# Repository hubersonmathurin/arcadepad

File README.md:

# Arcadepad
Arcadepad is a 6 key retro-themed macropad. It comes with a rotary encoder, an OLED display, and utilizes kmk firmware. The attached program allows switching through 3 layers, for a total of 18 commonly used 3d and 2d commands

This design was inspired by HackClub's HackPad tutorial
## Cad Model: Fusion 360

This macropad consists of 2 printed pieces, the case, which holds the PCB, and the cover. The PCB screws into 4 mounting holes, which will be filled with M3 bolts and heatset inserts, located at the bottom of the cover, not visible in picture. The case is held together with 4 more heatset inserts and M3 boots. 
## PCB: KiCad

## Bill Of Materials
- Cherry MX Switches(6)
- Blank DSA Keycaps(6)
- Seeed XIAO RP2040(1)
- EC11 Rotary Encoder(1)
- SSD1306 OLED Display(1)
- M3X13 Screws(8)
- M3x5mmx4mm Heatset Inserts(8)
- 3D Printes Case & Cover(1)

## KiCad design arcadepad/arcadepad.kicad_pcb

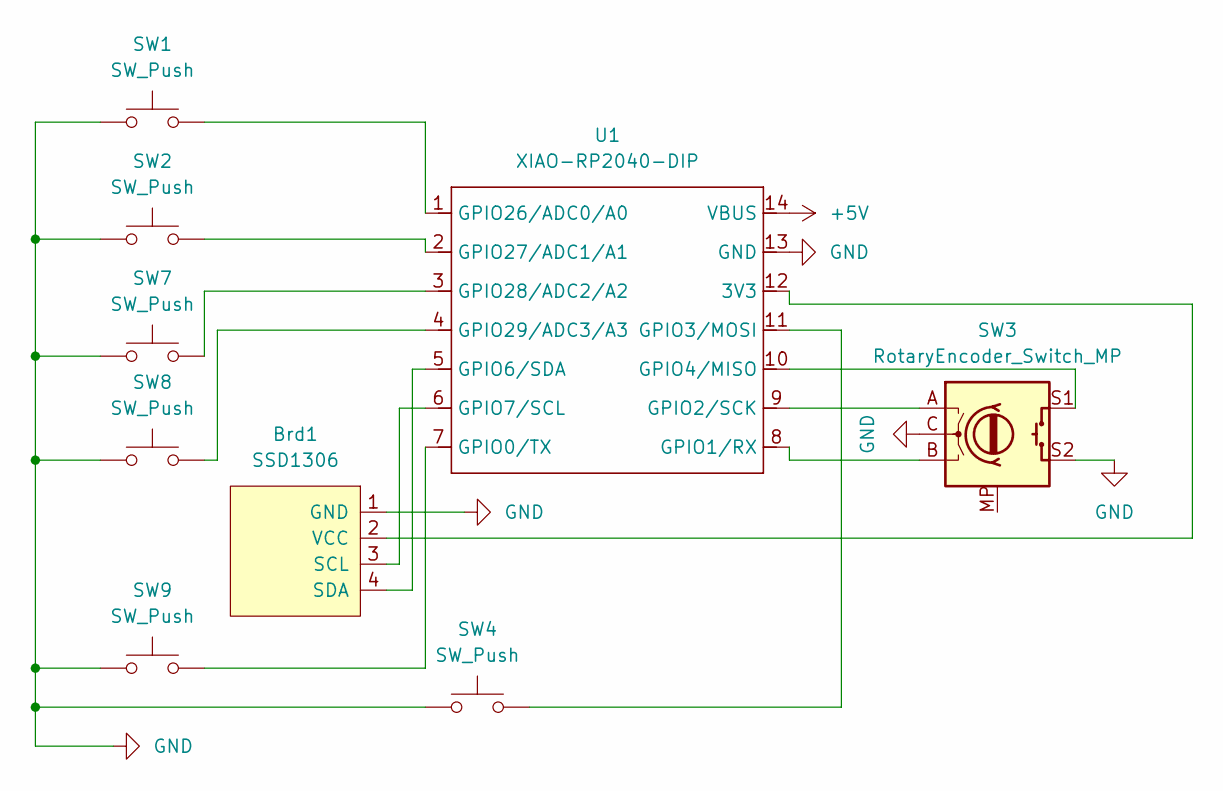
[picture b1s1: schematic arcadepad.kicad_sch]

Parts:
Brd1: SSD1306; OLED_0.91_128x32
SW1, SW2, SW4, SW7, SW8, SW9: SW_Push; SW_Cherry_MX_1.00u_PCB
SW3: RotaryEncoder_Switch_MP; RotaryEncoder_Alps_EC11E-Switch_Vertical_H20mm_CircularMoun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
U1: XIAO-RP2040-DIP

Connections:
+5V: U1.14 (VBUS)
GND: Brd1.1 (GND), SW1.1, SW2.1, SW3.C, SW3.S2, SW4.1, SW7.1, SW8.1, SW9.1, U1.13 (GND)
unnamed: Brd1.3 (SCL), U1.6 (GPIO7/SCL)
unnamed: Brd1.4 (SDA), U1.5 (GPIO6/SDA)
unnamed: Brd1.2 (VCC), U1.12 (3V3)
unnamed: SW9.2, U1.7 (GPIO0/TX)
unnamed: SW3.B, U1.8 (GPIO1/RX)
unnamed: SW3.A, U1.9 (GPIO2/SCK)
unnamed: SW4.2, U1.11 (GPIO3/MOSI)
unnamed: SW3.S1, U1.10 (GPIO4/MISO)
unnamed: SW1.2, U1.1 (GPIO26/ADC0/A0)
unnamed: SW2.2, U1.2 (GPIO27/ADC1/A1)
unnamed: SW7.2, U1.3 (GPIO28/ADC2/A2)
unnamed: SW8.2, U1.4 (GPIO29/ADC3/A3)

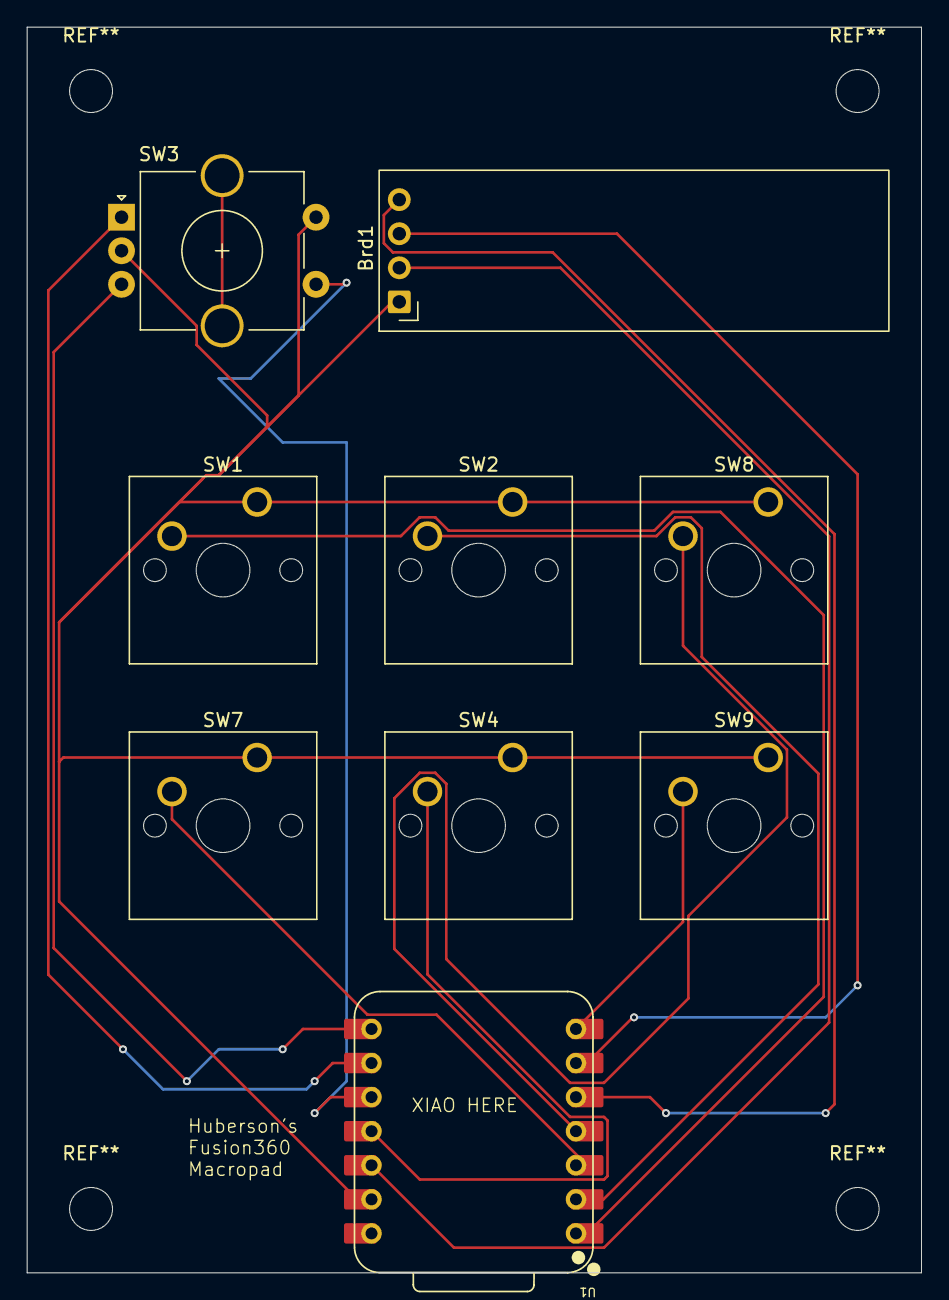
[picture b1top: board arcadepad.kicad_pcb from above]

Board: 2 copper layers, 66.7 x 92.9 mm, 9 parts (0 on the bottom side), 13 nets.

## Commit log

2026-02-04 Create fullcad
2026-02-04 Rename Screenshot 2026-02-03 at 8.58.20 PM.png to fullCad
2026-02-04 Rename Screenshot 2026-02-03 at 8.59.49 PM.png to schematic
2026-02-04 Rename fullcad to fullcad.png
2026-02-04 Rename schematic to schematic.png
2026-02-04 Rename Screenshot 2026-02-03 at 9.00.08 PM.png to pcb2D.png
2026-02-04 Rename Screenshot 2026-02-03 at 9.00.20 PM.png to pcb3D.png
2026-02-04 Rename Screenshot 2026-02-03 at 9.01.29 PM.png to case.png
2026-02-04 Create h
2026-02-04 Rename Screenshot 2026-02-04 143304.png to newFullCad.png
2026-02-04 Rename Screenshot 2026-02-04 144054.png to newSchematic.png
2026-02-04 Rename Screenshot 2026-02-04 144325.png to newPcb.png
2026-02-04 Update images and PCB details in README
    Updated images and PCB information in the README.
2026-02-05 Create a
2026-02-05 Rename FinalMacropad.step to FinalMacropad.step
2026-02-05 Rename arcadepad.kicad_pcb to arcadepad.kicad_pcb
2026-02-05 Rename arcadepad.kicad_sch to arcadepad.kicad_sch
2026-02-05 Rename arcadepad.kicad_pro to arcadepad.kicad_pro
2026-02-05 Rename main.py to main.py
